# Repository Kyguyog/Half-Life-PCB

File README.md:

This repo is for my firsty project ever for Hack Club's Half Life Program, my project is a macropad with a screen, 4 MX Cherry Key switches, and built on a esp32s3

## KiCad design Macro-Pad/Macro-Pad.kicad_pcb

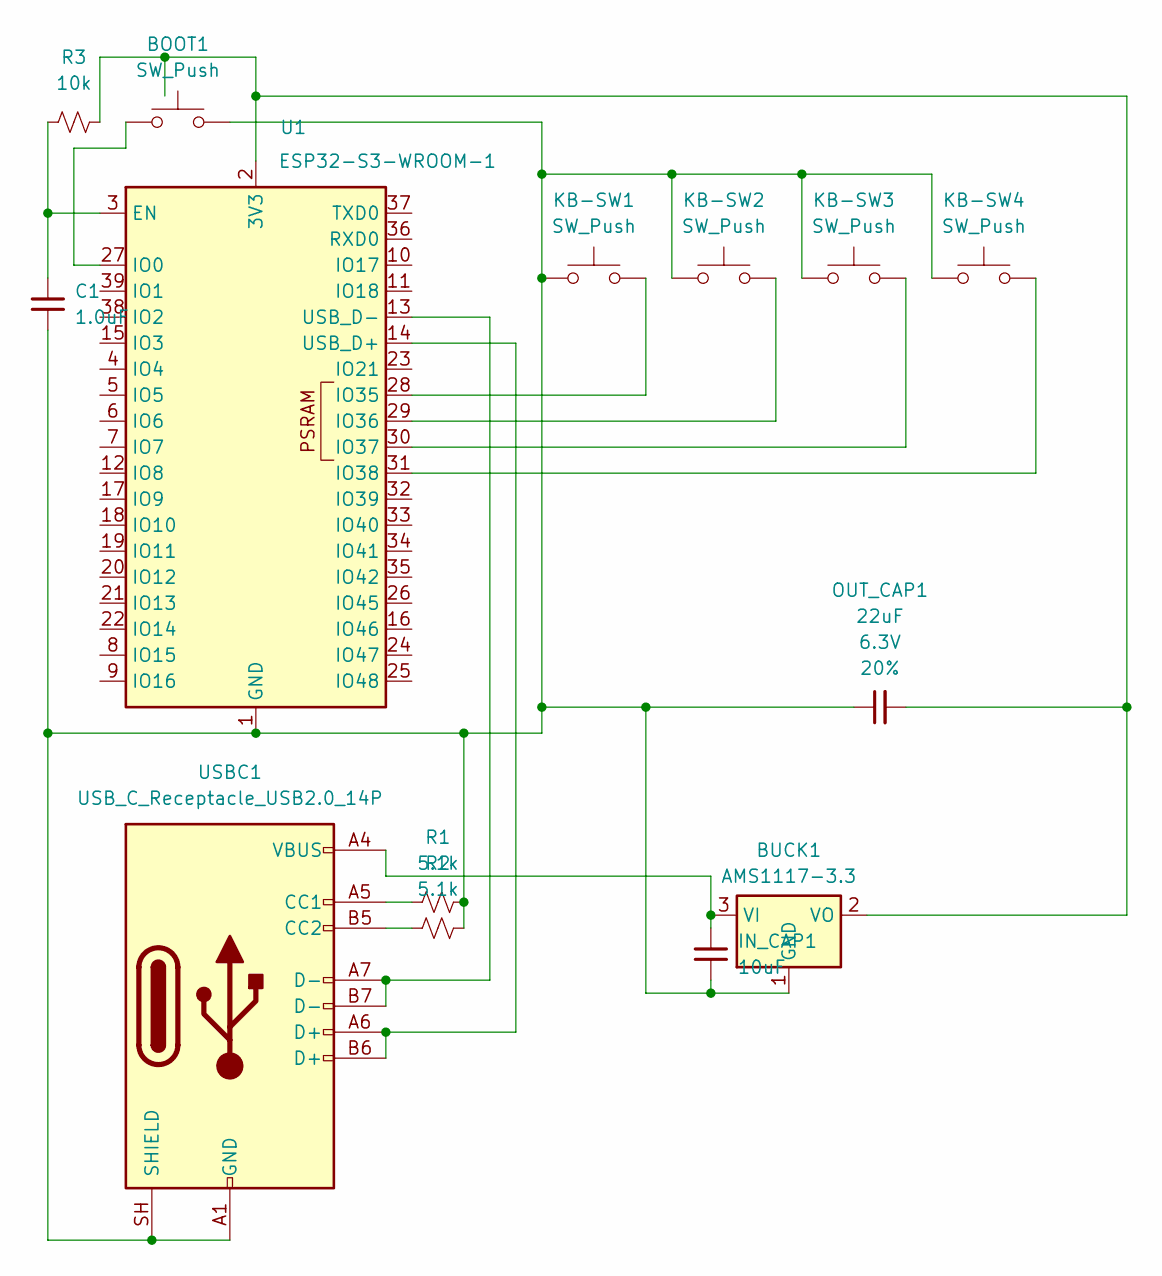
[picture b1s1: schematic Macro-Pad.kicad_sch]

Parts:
BOOT1: SW_Push; SW_Push_SPST_NO_Alps_SKRK
BUCK1: AMS1117-3.3; SOT-223-3_TabPin2
C1: 1.0uF; C_0805_2012Metric_Pad1.18x1.45mm_HandSolder
IN_CAP1: 10uF; C_0805_2012Metric_Pad1.18x1.45mm_HandSolder
KB-SW1, KB-SW2, KB-SW3, KB-SW4: SW_Push; SW_Cherry_MX_1.00u_PCB
OUT_CAP1: 22uF; C_0805_2012Metric_Pad1.18x1.45mm_HandSolder; Voltage 6.3V; Tolerance 20%
R1, R2: 5.1k; R_0805_2012Metric_Pad1.20x1.40mm_HandSolder
R3: 10k; R_0805_2012Metric_Pad1.20x1.40mm_HandSolder
U1: ESP32-S3-WROOM-1
USBC1: USB_C_Receptacle_USB2.0_14P; USB_C_Receptacle_HRO_TYPE-C-31-M-12

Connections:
unnamed: BOOT1.2, BUCK1.1 (GND), C1.2, IN_CAP1.2, KB-SW1.1, KB-SW2.1, KB-SW3.1, KB-SW4.1, OUT_CAP1.1, R1.2, R2.2, U1.1 (GND), U1.40 (GND), U1.41 (GND), USBC1.A1 (GND), USBC1.A12 (GND), USBC1.B1 (GND), USBC1.B12 (GND), USBC1.SH (SHIELD)
unnamed: BUCK1.3 (VI), IN_CAP1.1, USBC1.A4 (VBUS), USBC1.A9 (VBUS), USBC1.B4 (VBUS), USBC1.B9 (VBUS)
unnamed: BUCK1.2 (VO), OUT_CAP1.2, R3.2, U1.2 (3V3)
unnamed: C1.1, R3.1, U1.3 (EN)
unnamed: BOOT1.1, U1.27 (IO0)
unnamed: KB-SW1.2, U1.28 (IO35)
unnamed: KB-SW2.2, U1.29 (IO36)
unnamed: KB-SW3.2, U1.30 (IO37)
unnamed: KB-SW4.2, U1.31 (IO38)
unnamed: U1.14 (USB_D+), USBC1.A6 (D+), USBC1.B6 (D+)
unnamed: U1.13 (USB_D-), USBC1.A7 (D-), USBC1.B7 (D-)
unnamed: R1.1, USBC1.A5 (CC1)
unnamed: R2.1, USBC1.B5 (CC2)

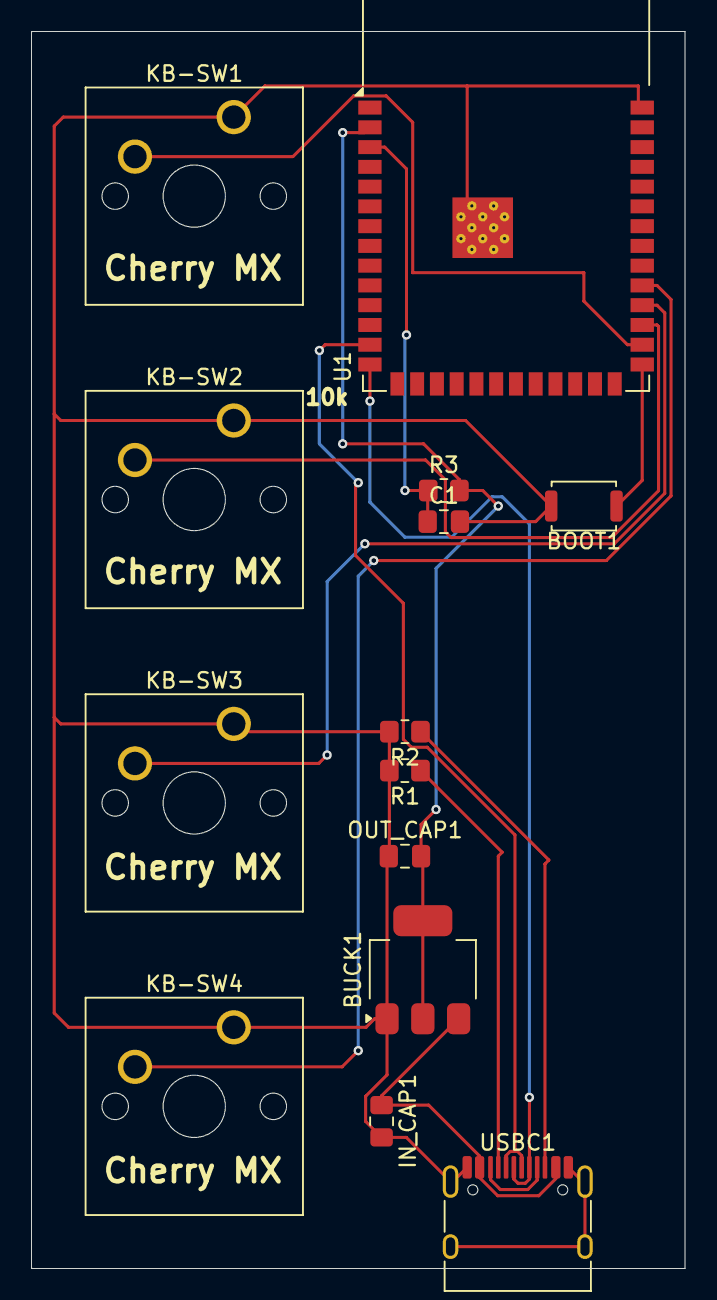
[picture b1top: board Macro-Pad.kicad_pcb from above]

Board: 2 copper layers, 42.0 x 79.5 mm, 14 parts (0 on the bottom side), 13 nets.

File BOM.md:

# Macro Pad – bill of materials

<!-- Generated by Half Life from project cmuw3mqt905k401osph62bah5. Edits here are overwritten on the next sync. -->
<!-- Generated: 2026-10-10T19:29:29.108Z -->

> [!NOTE]
> This parts list is mirrored from [Half Life](https://halflife.hackclub.com). Editing it here will not change the platform's copy, and the next sync overwrites this file.

| Week | Tier | Parts funding |
| --- | --- | --- |
| Week 1 | Tier 1 | $30.00 |

| Part | What it's for | Qty | Unit | Total | Vendor |
| --- | --- | --- | --- | --- | --- |
| SW_Push - SW_SPST_PTS645Sx43SMTR92 | — | 1 | $0.00 | $0.00 | C&K Switches |
| USB_C_Receptacle_USB2.0_14P - USB_C_Receptacle_HRO_TYPE-C-31-M-12 | — | 1 | $0.00 | $0.00 | HRO (Korean Hroparts) |
| SW_Push - SW_Cherry_MX_1.00u_PCB | — | 4 | $0.00 | $0.00 | Cherry |
| ESP32-S3-WROOM-1 | — | 1 | $0.00 | $0.00 | Espressif Systems |
| TPS62162DSG Voltage Regulator | — | 1 | $0.00 | $0.00 | Texas Instruments |
| **Parts subtotal** | — | — | — | **$0.00** | — |
| **Tax & shipping** | — | — | — | **$0.00** | — |
| **Total** | — | — | — | **$0.00** | — |

$30.00 left of the tier's funding.
